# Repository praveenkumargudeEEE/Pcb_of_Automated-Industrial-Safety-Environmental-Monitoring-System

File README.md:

# Pcb_of_Automated-Industrial-Safety-Environmental-Monitoring-System
Pcb of Automated Industrial Safety Environmental Monitoring System

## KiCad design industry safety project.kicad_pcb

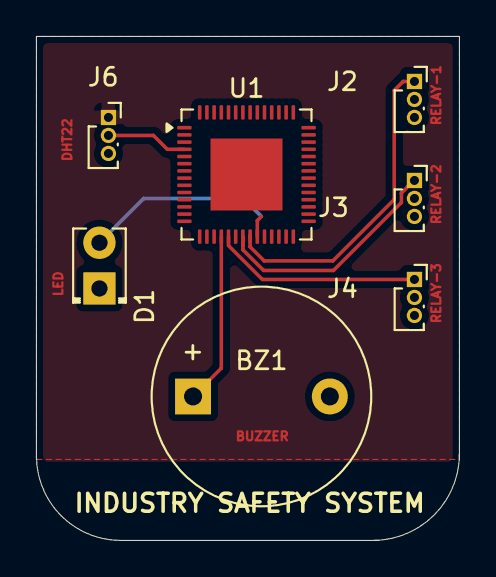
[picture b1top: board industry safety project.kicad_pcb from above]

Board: 2 copper layers, 23.5 x 28.0 mm, 7 parts (0 on the bottom side), 8 nets.

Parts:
BZ1: Buzzer; Buzzer_12x9.5RM7.6
D1: LED; LED_D2.0mm_W4.0mm_H2.8mm_FlatTop
J2: Relay_1; PinSocket_1x03_P1.00mm_Vertical
J3: Relay_2; PinSocket_1x03_P1.00mm_Vertical
J4: Relay_3; PinSocket_1x03_P1.00mm_Vertical
J6: DHT22; PinSocket_1x03_P1.00mm_Vertical
U1: ESP32-S3; QFN-56-1EP_7x7mm_P0.4mm_EP4x4mm

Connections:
+3V3: J2.2, J3.2, J4.2, J6.1, U1.55 (VDDA), U1.56 (VDDA)
GND: BZ1.2 (-), D1.1 (K), J2.3, J3.3, J4.3, J6.3, U1.57 (GND)
unnamed: BZ1.1 (+), U1.18 (GPIO13)
unnamed: D1.2 (A), U1.23 (GPIO17)
unnamed: J2.1, U1.22 (XTAL_32K_N)
unnamed: J3.1, U1.21 (XTAL_32K_P)
unnamed: J4.1, U1.19 (GPIO14)
unnamed: J6.2, U1.4 (CHIP_PU)
